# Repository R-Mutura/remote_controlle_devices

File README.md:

# remote_controlle_devices
The repo is only filled with the relevant files.
the project was too large to be accomodated here.

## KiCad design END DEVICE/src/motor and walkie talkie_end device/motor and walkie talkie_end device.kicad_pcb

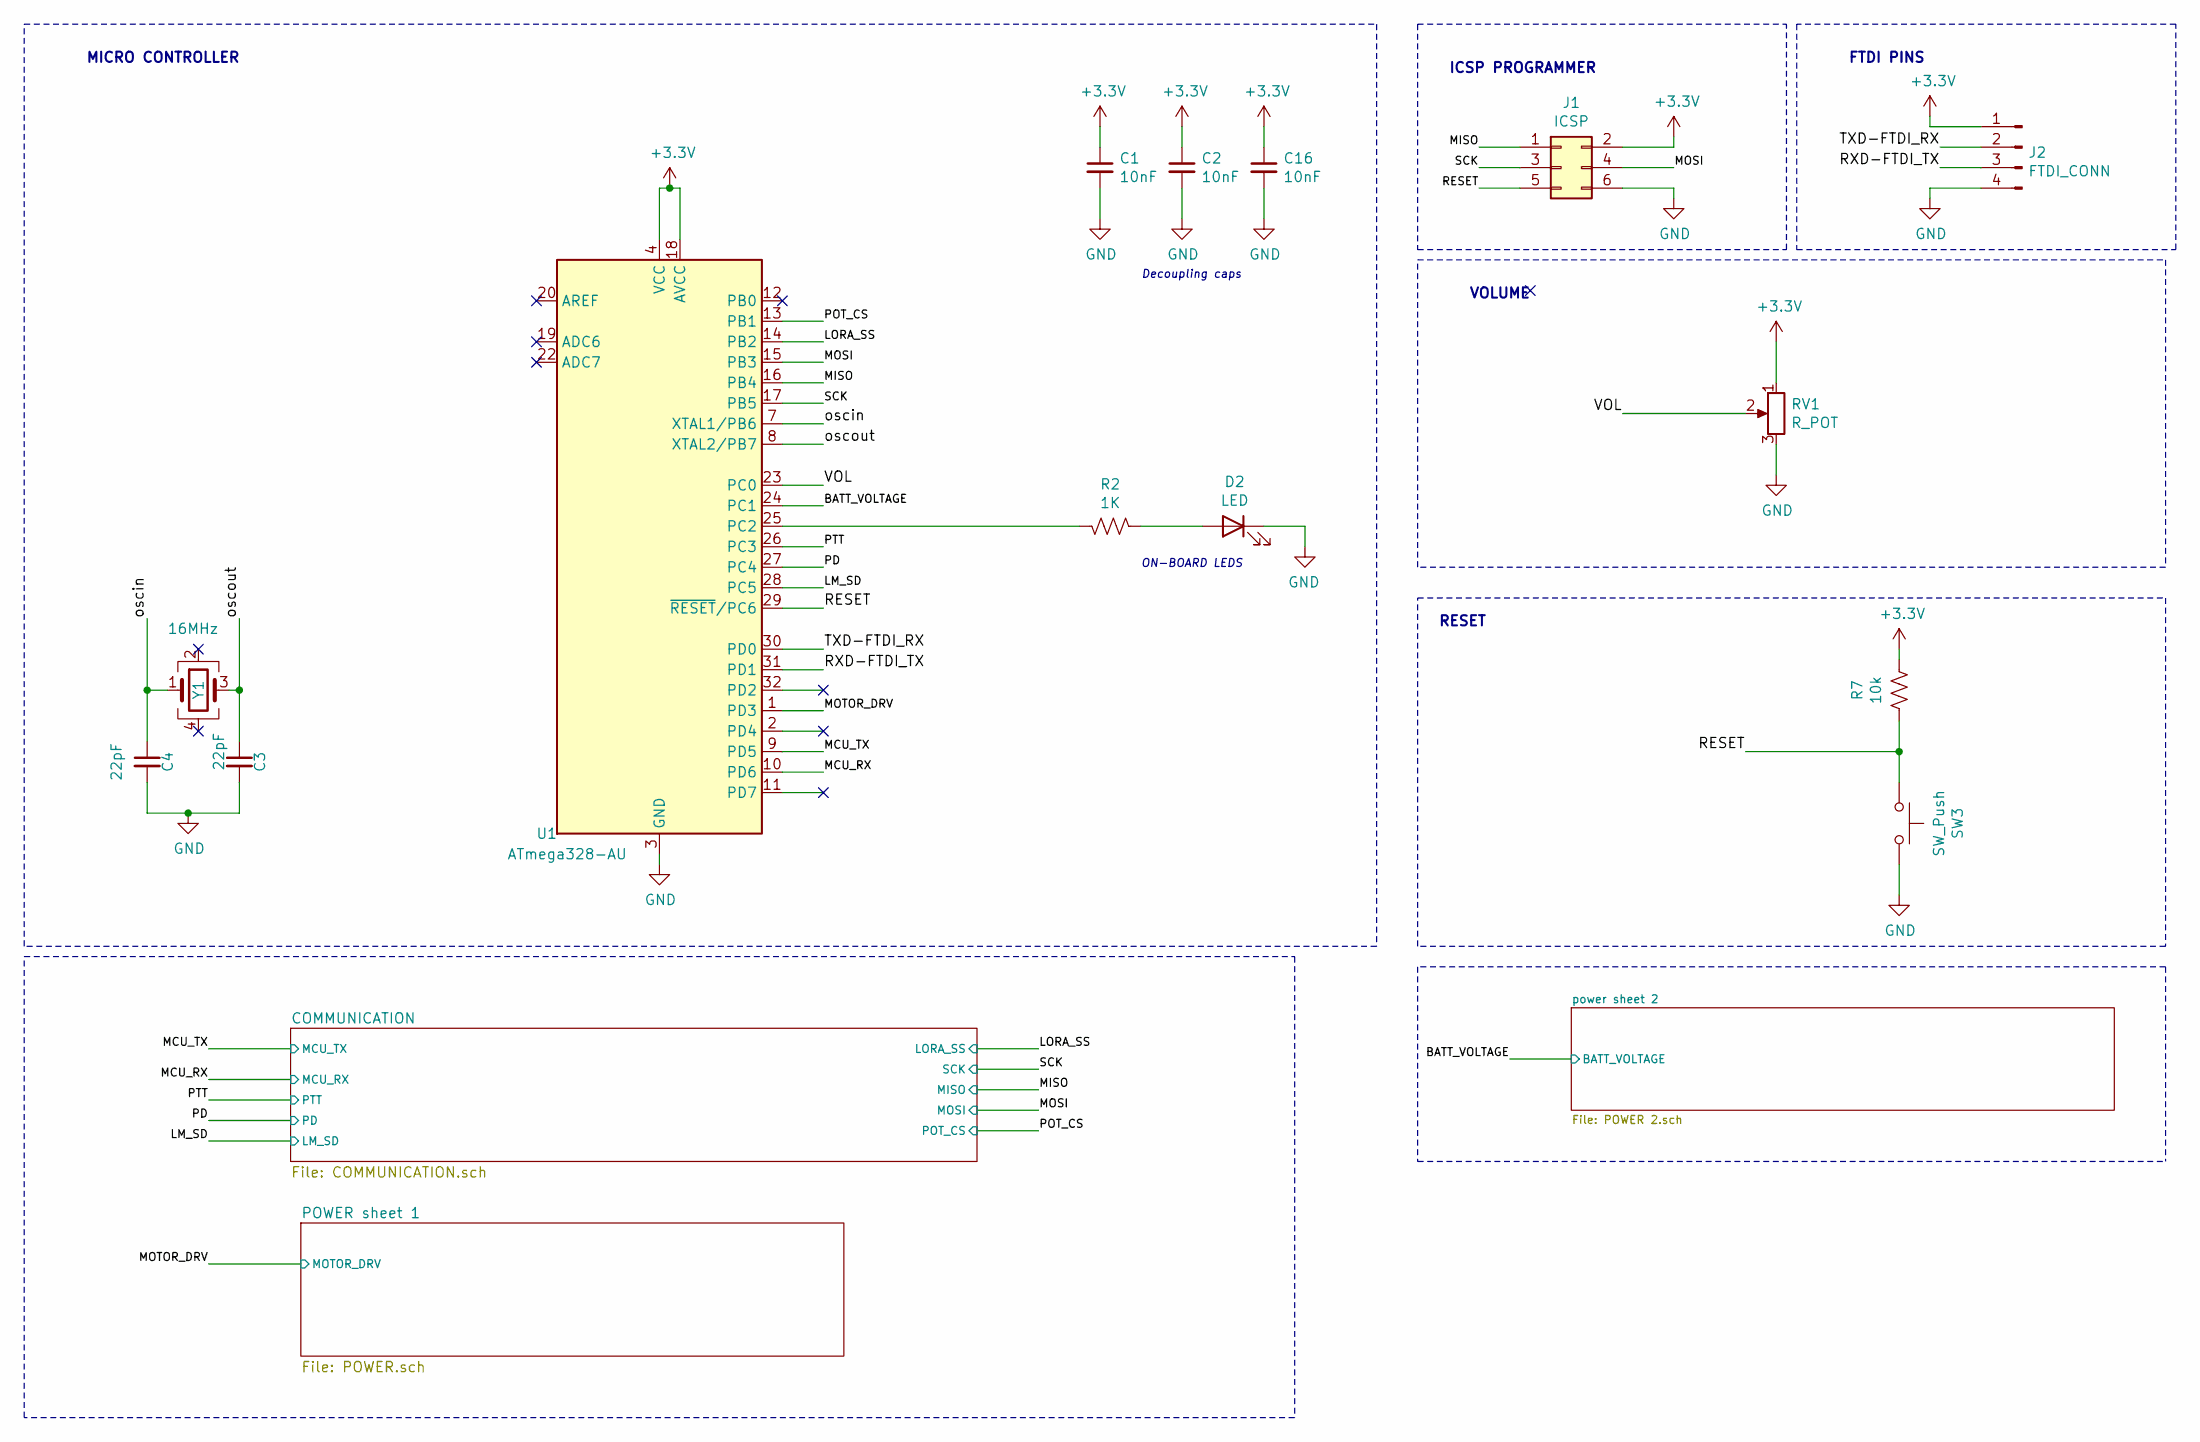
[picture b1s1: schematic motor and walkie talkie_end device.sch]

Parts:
C1, C2, C16: 10nF; C_0603_1608Metric
C3, C4: 22pF; C_0603_1608Metric
D2: LED; LED_0603_1608Metric
J1: ICSP; PinHeader_2x03_P2.54mm_Vertical
J2: FTDI_CONN; PinHeader_1x04_P2.54mm_Vertical
R2: 1K; R_0603_1608Metric
R7: 10k; R_0603_1608Metric
RV1: R_POT; Potentiometer_Vishay_148-149_Single_Horizontal
SW3: SW_Push; SW_SPST_B3U-1000P
U1: ATmega328-AU; TQFP-32_7x7mm_P0.8mm
Y1: 16MHz; Crystal_SMD_Abracon_ABM8G-4Pin_3.2x2.5mm

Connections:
+3V3: C1.1, C2.1, C16.1, J1.2, J2.1, R7.2, RV1.1, U1.4 (VCC), U1.6 (VCC), U1.18 (AVCC); also elsewhere on the board
/BATT_VOLTAGE: U1.24 (PC1); also elsewhere on the board
/LM_SD: U1.28 (PC5); also elsewhere on the board
/LORA_SS: U1.14 (PB2); also elsewhere on the board
/MCU_RX: U1.10 (PD6); also elsewhere on the board
/MCU_TX: U1.9 (PD5); also elsewhere on the board
/MISO: J1.1, U1.16 (PB4); also elsewhere on the board
/MOSI: J1.4, U1.15 (PB3); also elsewhere on the board
/MOTOR_DRV: U1.1 (PD3); also elsewhere on the board
/PD: U1.27 (PC4); also elsewhere on the board
/POT_CS: U1.13 (PB1); also elsewhere on the board
/PTT: U1.26 (PC3); also elsewhere on the board
/RESET: J1.5, R7.1, SW3.1, U1.29 (~RESET~/PC6)
/RXD-FTDI_TX: J2.3, U1.31 (PD1)
/SCK: J1.3, U1.17 (PB5); also elsewhere on the board
/TXD-FTDI_RX: J2.2, U1.30 (PD0)
/VOL: RV1.2, U1.23 (PC0)
/oscin: C4.1, U1.7 (XTAL1/PB6), Y1.1
/oscout: C3.1, U1.8 (XTAL2/PB7), Y1.3
GND: C1.2, C2.2, C3.2, C4.2, C16.2, D2.1 (K), J1.6, J2.4, RV1.3, SW3.2, U1.3 (GND), U1.5 (GND), U1.21 (GND); also elsewhere on the board
unnamed: D2.2 (A), R2.2
unnamed: R2.1, U1.25 (PC2)

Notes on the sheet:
ICSP PROGRAMMER
FTDI PINS
VOLUME
RESET
MICRO CONTROLLER
Decoupling caps
ON-BOARD LEDS

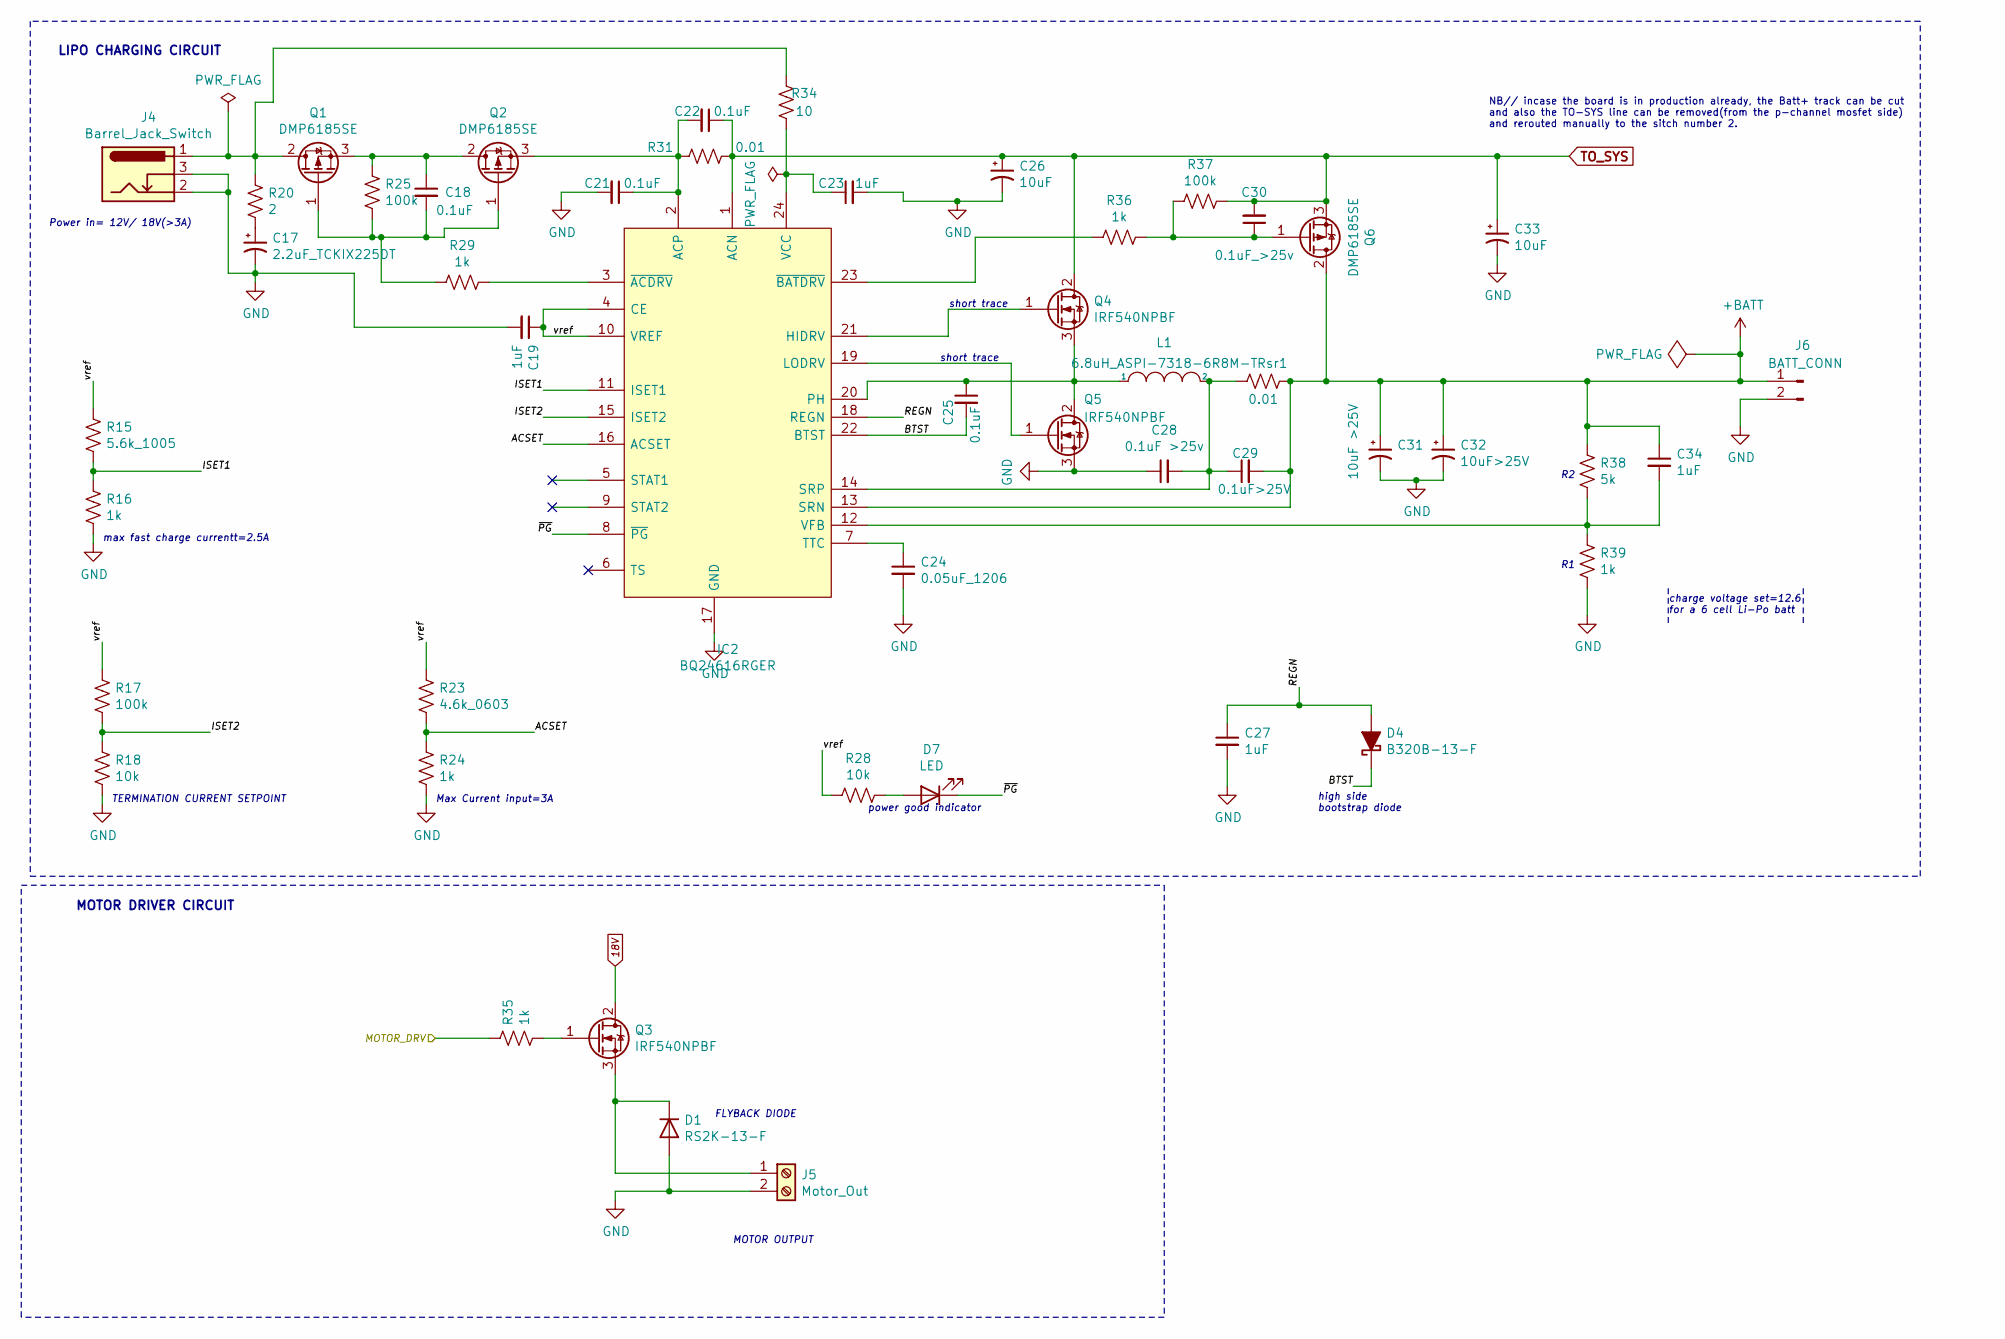
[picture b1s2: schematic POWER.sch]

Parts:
C17: 2.2uF_TCKIX225DT; CP_EIA-7343-31_Kemet-D
C18, C21, C22, C25: 0.1uF; C_0603_1608Metric
C19, C23, C27, C34: 1uF; C_0603_1608Metric
C24: 0.05uF_1206; C_0603_1608Metric
C26, C33: 10uF; CP_EIA-6032-28_Kemet-C
C28: 0.1uF >25v; C_0603_1608Metric
C29: 0.1uF>25V; C_0603_1608Metric
C30: 0.1uF_>25v; C_0603_1608Metric
C31: 10uF >25V; CP_EIA-6032-28_Kemet-C
C32: 10uF>25V; CP_EIA-6032-28_Kemet-C
D1: RS2K-13-F; D_SMB_Handsoldering
D4: B320B-13-F; D_SMB_Handsoldering
D7: LED; LED_0603_1608Metric
IC2: BQ24616RGER; QFN-24-1EP_4x4mm_P0.5mm_EP2.6x2.6mm_ThermalVias; Mouser Part Number 595-BQ24616RGER
J4: Barrel_Jack_Switch; BarrelJack_Horizontal
J5: Motor_Out; TerminalBlock_Altech_AK300-2_P5.00mm
J6: BATT_CONN; JST_PH_B2B-PH-K_1x02_P2.00mm_Vertical
L1: 6.8uH_ASPI-7318-6R8M-T; ASPI-7318-6R8M-T
Q1, Q2, Q6: DMP6185SE; SOT-223
Q3, Q4, Q5: IRF540NPBF; TO-220-3_Vertical
R15: 5.6k_1005; R_0402_1005Metric_Pad0.72x0.64mm_HandSolder
R16, R24, R29, R35, R36, R39: 1k; R_0603_1608Metric
R17, R25, R37: 100k; R_0603_1608Metric
R18, R28: 10k; R_0603_1608Metric
R20: 2; R_0603_1608Metric
R23: 4.6k_0603; R_0603_1608Metric
R31: 0.01; R_0603_1608Metric
R34: 10; R_0603_1608Metric
R38: 5k; R_0603_1608Metric
Rsr1: 0.01; R_0603_1608Metric

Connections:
18V: Q3.2 (D); also elsewhere on the board
+BATT: C29.2, C31.1, C32.1, C34.1, IC2.13 (SRN), J6.1, Q6.2 (D), Q6.4 (D), R38.1, Rsr1.1
/MOTOR_DRV: R35.2; also elsewhere on the board
/POWER sheet 1/ACSET: IC2.16 (ACSET), R23.2, R24.1
/POWER sheet 1/BTST: C25.2, D4.1 (K), IC2.22 (BTST)
/POWER sheet 1/ISET1: IC2.11 (ISET1), R15.2, R16.1
/POWER sheet 1/ISET2: IC2.15 (ISET2), R17.2, R18.1
/POWER sheet 1/REGN: C27.1, D4.2 (A), IC2.18 (REGN)
/POWER sheet 1/vref: C19.1, IC2.4 (CE), IC2.10 (VREF), R15.1, R17.1, R23.1, R28.2
/POWER sheet 1/~PG: D7.1 (K), IC2.8 (~PG); also elsewhere on the board
GND: C17.2, C19.2, C21.2, C23.2, C24.2, C26.2, C27.2, C28.1, C31.2, C32.2, C33.2, D1.2 (A), IC2.17 (GND), J4.2, J4.3, J5.2, J6.2, Q5.3 (S), R16.2, R18.2, R24.2, R39.2; also elsewhere on the board
unnamed: C17.1, R20.2
unnamed: C18.1, Q1.3 (S), Q2.2 (D), Q2.4 (D), R25.1
unnamed: C18.2, Q1.1 (G), Q2.1 (G), R25.2, R29.2
unnamed: C21.1, C22.2, IC2.2 (ACP), Q2.3 (S), R31.2
unnamed: C23.1, IC2.24 (VCC), R34.2
unnamed: C24.1, IC2.7 (TTC)
unnamed: C25.1, IC2.20 (PH), L1.1, Q4.3 (S), Q5.2 (D)
unnamed: C28.2, C29.1, IC2.14 (SRP), L1.2, Rsr1.2
unnamed: C30.1, Q6.1 (G), R36.1, R37.2
unnamed: C34.2, IC2.12 (VFB), R38.2, R39.1
unnamed: D1.1 (K), J5.1, Q3.3 (S)
unnamed 54: D7.2 (A), R28.1; also elsewhere on the board
unnamed: IC2.3 (~ACDRV), R29.1
unnamed: IC2.19 (LODRV), Q5.1 (G)
unnamed: IC2.21 (HIDRV), Q4.1 (G)
unnamed: IC2.23 (~BATDRV), R36.2
unnamed: J4.1, Q1.2 (D), Q1.4 (D), R20.1, R34.1
unnamed: Q3.1 (G), R35.1
TO_SYS: C22.1, C26.1, C30.2, C33.1, IC2.1 (ACN), Q4.2 (D), Q6.3 (S), R31.1, R37.1; also elsewhere on the board

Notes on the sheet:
MOTOR DRIVER CIRCUIT
short trace
power good indicator
high side bootstrap diode
charge voltage set=12.6 for a 6 cell Li-Po batt
max fast charge currentt=2.5A
Max Current input=3A
TERMINATION CURRENT SETPOINT
Power in= 12V/ 18V(>3A)
LIPO CHARGING CIRCUIT
FLYBACK DIODE
MOTOR OUTPUT
NB// incase the board is in production already, the Batt+ track can be cut and also the TO-SYS line can be removed(from the p-channel mosfet side) and rerouted manually to the sitch number 2.

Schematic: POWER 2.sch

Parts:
C5: 10uF; C_0603_1608Metric
C35: 10uF; CP_Elec_4x4.5
C36: 10uF_50V; CP_EIA-1608-08_AVX-J
C37, C38, C44, C47: 1uF; C_0603_1608Metric
C39: 27nF; C_0603_1608Metric
C40: 4.7uF _3.705mOhm; C_0603_1608Metric
C41: 100nF; C_0603_1608Metric
C42: 100nF_0.064ohm; C_0603_1608Metric
C43: 8.2nF; C_0603_1608Metric
C45: 2.2uF; CP_EIA-2012-12_Kemet-R_Pad1.30x1.05mm_HandSolder
C46, C50: 10uF; CP_EIA-2012-12_Kemet-R_Pad1.30x1.05mm_HandSolder
C48: 0.1uF; C_0603_1608Metric
C49: 1uF; CP_EIA-2012-12_Kemet-R_Pad1.30x1.05mm_HandSolder
D3: LED; LED_0603_1608Metric
D11: DIODE SCHOTTKY 200V 10A DPAK; TO-252-3_TabPin2
IC4: TPS55340RTER; WQFN-16-1EP_3x3mm_P0.5mm_EP1.75x1.75mm_ThermalVias
L2: 6.8uH_17mOHM; ASPI-7318-6R8M-T
R1: 10k; R_0603_1608Metric
R40, R42, R43: 60.4K; R_0603_1608Metric
R41: 931; R_0603_1608Metric
R44: 28.2k; R_0603_1608Metric
R45: 10; R_0603_1608Metric
SW6: SW_SPDT; SW_SPDT_PCM12
U6: LM1117-3.3(; SOT-223
U9: L4931ABDT50; TO-252-3_TabPin2

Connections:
18V: C5.1, D11.2 (A), R42.1; also elsewhere on the board
+3V3: C48.1, C49.1, R1.2, U6.2 (VO); also elsewhere on the board
+5V: C44.1, C45.1, C46.1, C47.1, C50.1, U6.3 (VI), U9.3 (VO); also elsewhere on the board
/BATT_VOLTAGE: R44.2, R45.1; also elsewhere on the board
/power sheet 2/BATT_IN: C35.1, C36.1, C37.1, C38.1, C40.1, C42.1, IC4.2 (VIN), IC4.3 (EN), L2.1, R44.1, SW6.3 (C), U9.1 (VI)
GND: C5.2, C35.2, C36.2, C37.2, C38.2, C39.2, C40.2, C41.2, C42.2, C43.2, C44.2, C45.2, C46.2, C47.2, C48.2, C49.2, C50.2, D3.1 (K), IC4.6 (AGND), IC4.10 (NC_1), IC4.11 (PGND_1), IC4.12 (PGND_2), IC4.13 (PGND_3), IC4.14 (NC_2), IC4.17 (PowerPAD), R40.2, R43.2, R45.2, U6.1 (GND), U9.2 (GND); also elsewhere on the board
unnamed: C39.1, IC4.4 (SS)
unnamed: C41.1, R41.2
unnamed: C43.1, IC4.7 (COMP), R41.1
unnamed: D3.2 (A), R1.1
unnamed: D11.1 (K), IC4.1 (SW_1), IC4.15 (SW_2), IC4.16 (SW_3), L2.2
unnamed: IC4.8 (FB), R42.2, R43.1
unnamed: IC4.9 (FREQ), R40.1
TO_SYS: SW6.2 (B); also elsewhere on the board

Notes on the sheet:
11.1V to 18V boost circuit
Vin=11.1v Vout=18v Iout=1A
ON / OFF SWITCH
3.3V REGULATOR
5V REGULATOR
BATTERY MONITORING CIRCUIT
Regulator can handle up to 20V input from TO_SYS & BATT_IN
NB// All components can work when power is pluggedin except the DC-Motor. The motor only works when the battery is connected
SYSTEM_ON

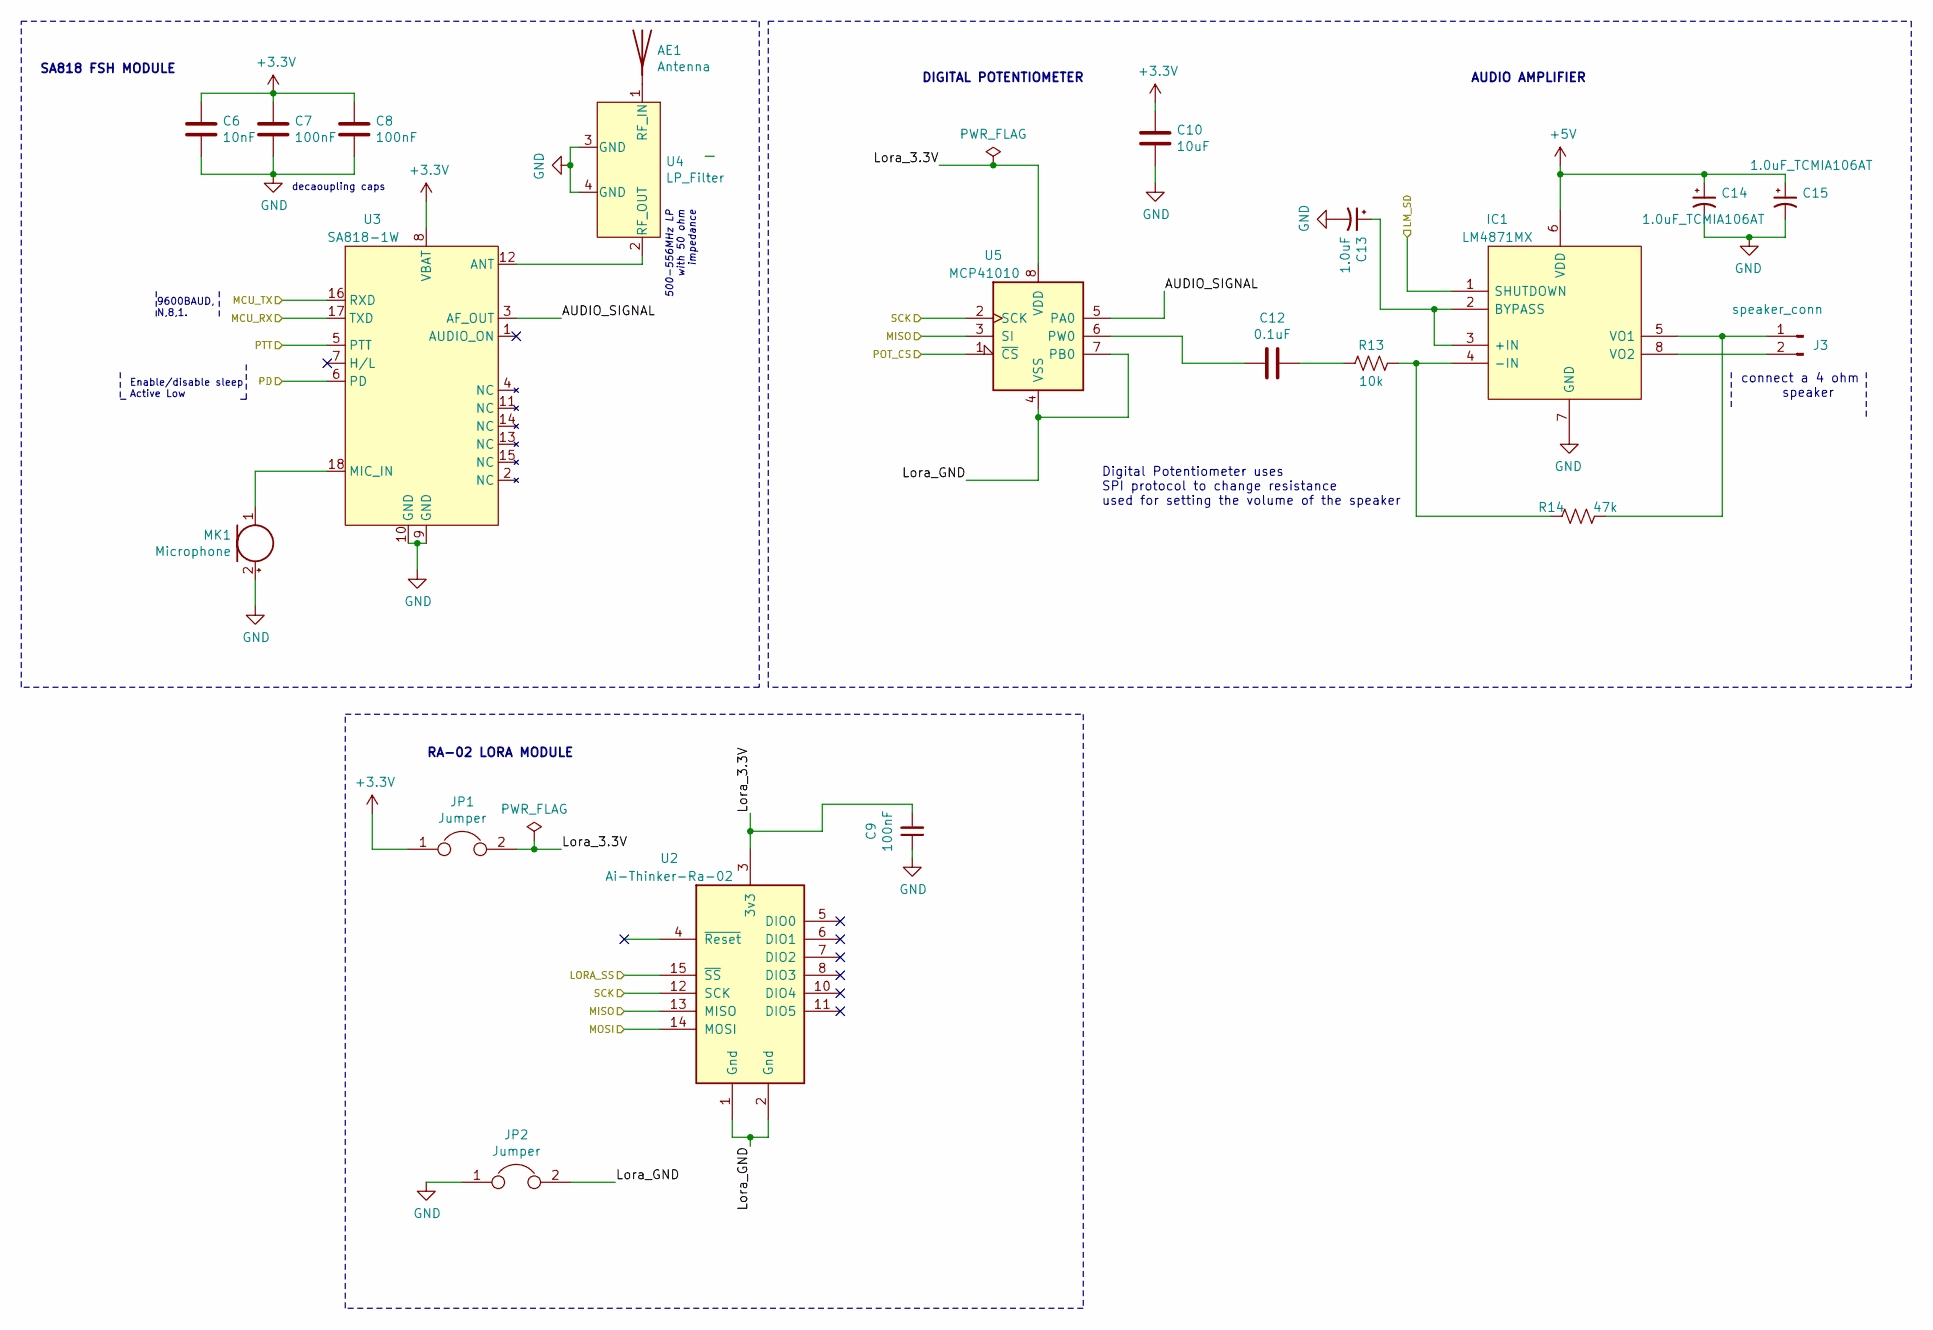
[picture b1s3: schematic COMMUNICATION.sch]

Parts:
AE1: Antenna; SMA_Amphenol_901-144_Vertical
C6: 10nF; C_0603_1608Metric
C7, C8, C9: 100nF; C_0603_1608Metric
C10: 10uF; C_0603_1608Metric
C12: 0.1uF; C_0603_1608Metric
C13: 1.0uF; CP_EIA-2012-12_Kemet-R
C14, C15: 1.0uF_TCMIA106AT; CP_EIA-2012-12_Kemet-R
IC1: LM4871MX; SOP-8_3.9x4.9mm_P1.27mm; Mouser Part Number 926-LM4871MMX/NOPB
J3: speaker_conn; JST_PH_B2B-PH-K_1x02_P2.00mm_Vertical
JP1, JP2: Jumper; TestPoint_2Pads_Pitch2.54mm_Drill0.8mm
MK1: Microphone; CMEJ974537P
R13: 10k; R_0603_1608Metric
R14: 47k; R_0603_1608Metric
U2: Ai-Thinker-Ra-02; Ai-Thinker-Ra-01-LoRa
U3: SA818-1W
U4: LP_Filter; LFCN-530
U5: MCP41010; SOIC127P600X175-8N

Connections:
+3V3: C6.1, C7.1, C8.1, C10.1, JP1.1, U3.8 (VBAT); also elsewhere on the board
+5V: C14.1, C15.1, IC1.6 (VDD); also elsewhere on the board
/COMMUNICATION/AUDIO_SIGNAL: U3.3 (AF_OUT), U5.5 (PA0)
/COMMUNICATION/Lora_3.3V: C9.2, JP1.2, U2.3 (3v3), U5.8 (VDD)
/COMMUNICATION/Lora_GND: JP2.2, U2.1 (Gnd), U2.2 (Gnd), U2.9 (Gnd), U2.16 (Gnd), U5.4 (VSS), U5.7 (PB0)
/LM_SD: IC1.1 (SHUTDOWN); also elsewhere on the board
/LORA_SS: U2.15 (~SS); also elsewhere on the board
/MCU_RX: U3.17 (TXD); also elsewhere on the board
/MCU_TX: U3.16 (RXD); also elsewhere on the board
/MISO: U2.13 (MISO), U5.3 (SI); also elsewhere on the board
/MOSI: U2.14 (MOSI); also elsewhere on the board
/PD: U3.6 (PD); also elsewhere on the board
/POT_CS: U5.1 (~CS); also elsewhere on the board
/PTT: U3.5 (PTT); also elsewhere on the board
/SCK: U2.12 (SCK), U5.2 (SCK); also elsewhere on the board
GND: C6.2, C7.2, C8.2, C9.1, C10.2, C13.2, C14.2, C15.2, IC1.7 (GND), JP2.1, MK1.2 (+), U3.9 (GND), U3.10 (GND), U4.3 (GND), U4.4 (GND); also elsewhere on the board
unnamed: AE1.1, U4.1 (RF_IN)
unnamed: C12.1, R13.2
unnamed: C12.2, U5.6 (PW0)
unnamed: C13.1, IC1.2 (BYPASS), IC1.3 (+IN)
unnamed: IC1.4 (-IN), R13.1, R14.2
unnamed: IC1.5 (VO1), J3.1, R14.1
unnamed: IC1.8 (VO2), J3.2
unnamed: MK1.1 (-), U3.18 (MIC_IN)
unnamed: U3.12 (ANT), U4.2 (RF_OUT)

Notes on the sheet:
Enable/disable sleep Active Low
9600BAUD, N,8,1.
decaoupling caps
connect a 4 ohm speaker
DIGITAL POTENTIOMETER
AUDIO AMPLIFIER
SA818 FSH MODULE
RA-02 LORA MODULE
Digital Potentiometer uses SPI protocol to change resistance used for setting the volume of the speaker
500-556MHz LP with 50 ohm impedance

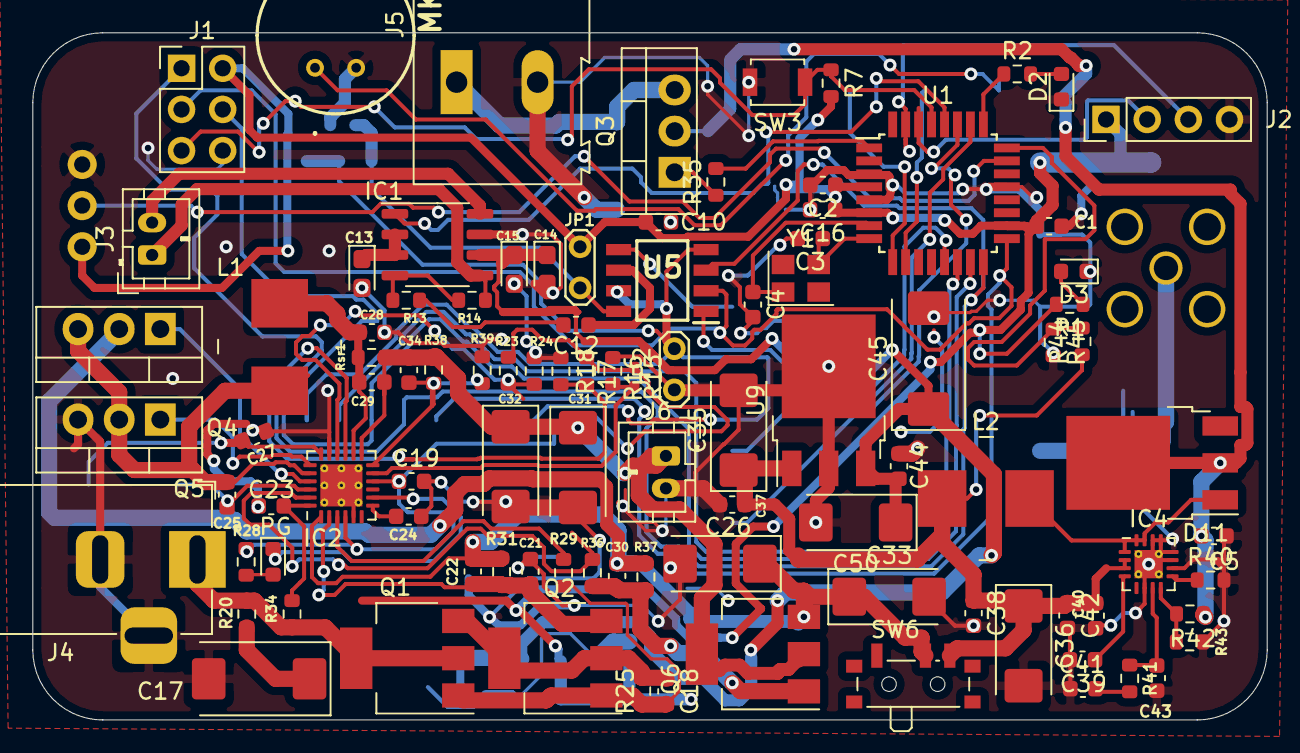
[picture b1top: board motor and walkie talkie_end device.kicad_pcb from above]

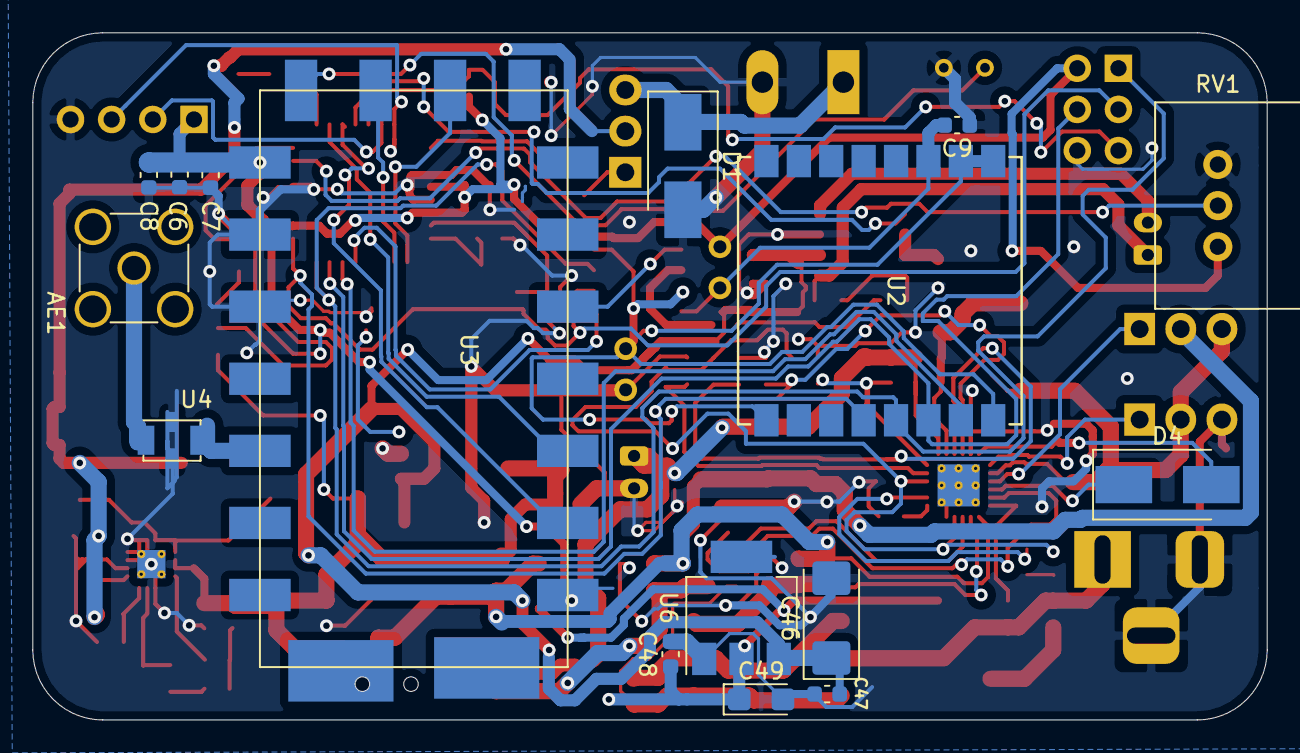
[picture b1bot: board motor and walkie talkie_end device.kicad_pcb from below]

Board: 2 copper layers, 76.2 x 42.4 mm, 115 parts (16 on the bottom side), 71 nets.

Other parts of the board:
PG: LED; LED_0603_1608Metric

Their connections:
/POWER sheet 1/~PG: PG.1; also elsewhere on the board
unnamed 54: PG.2; also elsewhere on the board

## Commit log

2021-08-26 Initial commit: complete schematic section 1- end device
2021-08-26 second commit: updated schematic symbol(oscillator)
2021-08-27 third commit:very minor changes
2021-08-27 commit 4:minor changes
2021-08-28 All footprint associations updated
2021-08-28 Project 99% complete and ready:Revision Needed
2021-08-29 Version 2 compressed board
2021-08-29 latest update
2021-08-29 Everythinhg is set
2021-08-29 All Set
2021-09-01 90% complete and. PCB done with tracks and design rules verified as well as dimensions
